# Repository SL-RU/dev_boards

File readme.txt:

This board is for almost any STM32Fxxx MCU with lqfp64 package. Exactly for: STM32F103RCT6

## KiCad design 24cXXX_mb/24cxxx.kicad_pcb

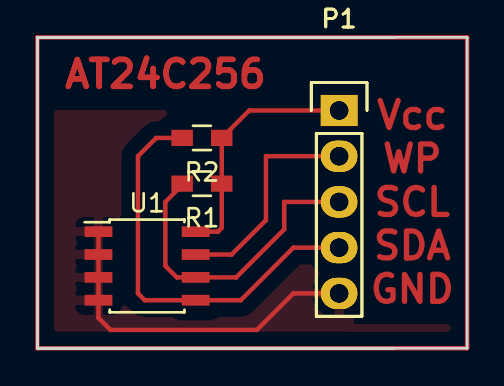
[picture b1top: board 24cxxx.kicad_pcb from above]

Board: 2 copper layers, 23.9 x 17.3 mm, 5 parts (0 on the bottom side), 5 nets.

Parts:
P1, P1#2: CONN_01X05; Pin_Header_Straight_1x05
R1, R2: 4.7k; R_0603_HandSoldering
U1: 24C512; SOIC-8_3.9x4.9mm_Pitch1.27mm

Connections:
unnamed: P1.1, P1#2.1, R1.1, R2.1, U1.8
unnamed: P1.2, P1#2.2, U1.7
unnamed: P1.3, P1#2.3, R1.2, U1.6
unnamed: P1.4, P1#2.4, R2.2, U1.5
unnamed: P1.5, P1#2.5, U1.1, U1.2, U1.3, U1.4

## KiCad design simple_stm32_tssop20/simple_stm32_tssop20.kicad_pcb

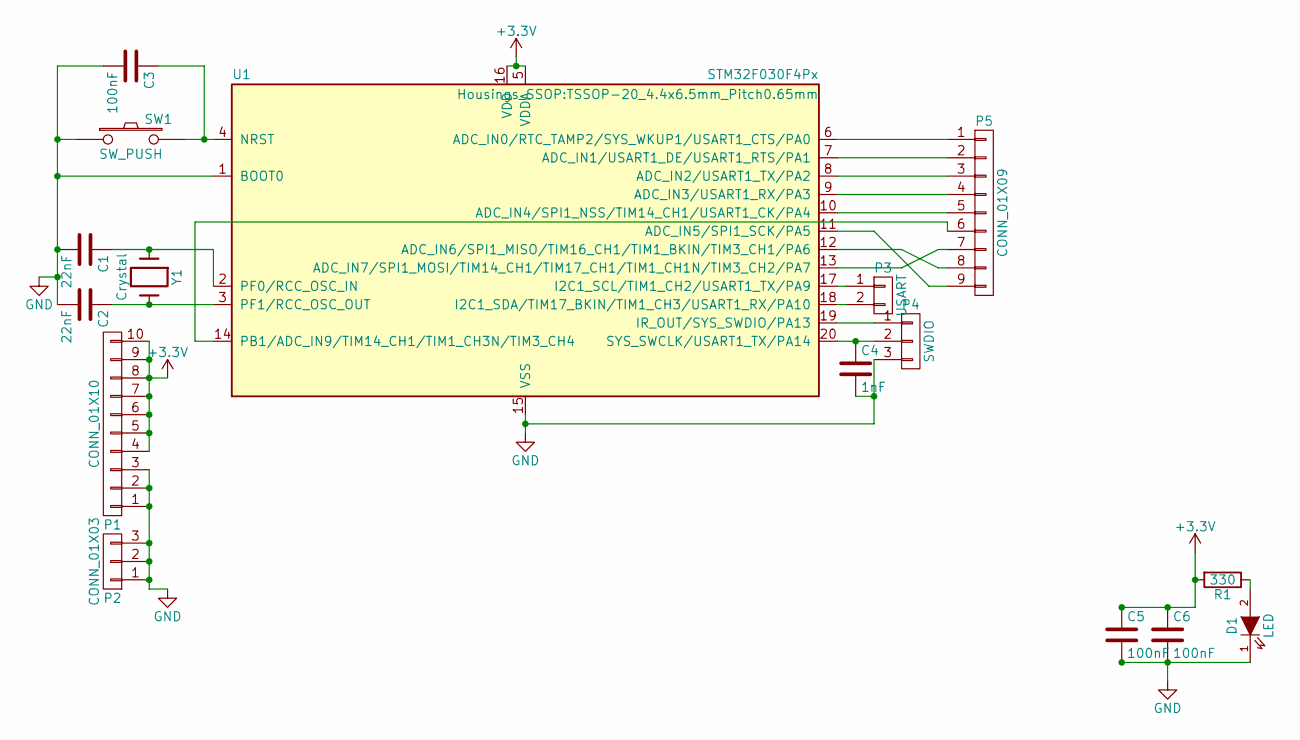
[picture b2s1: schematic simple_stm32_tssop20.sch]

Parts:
C1, C2: 22nF; C_0805_HandSoldering
C3, C5, C6: 100nF; C_0402
C4: 1nF; C_0402
D1: LED; LED-3MM
P1: CONN_01X10; Socket_Strip_Straight_1x10
P2: CONN_01X03; Socket_Strip_Straight_1x03
P3: USART; Socket_Strip_Straight_1x02
P4: SWDIO; Socket_Strip_Straight_1x03
P5: CONN_01X09; Socket_Strip_Straight_1x09
R1: 330; R_0603_HandSoldering
SW1: SW_PUSH; SW_PUSH_SMALL
U1: STM32F030F4Px; TSSOP-20_4.4x6.5mm_Pitch0.65mm
Y1: Crystal; Crystal_HC49-U_Vertical

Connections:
+3V3: C5.1, C6.1, P1.4, P1.5, P1.6, P1.7, P1.8, P1.9, P1.10, R1.2, U1.5 (VDDA), U1.16 (VDD)
GND: C1.2, C2.2, C3.2, C4.2, C5.2, C6.2, D1.1 (K), P1.1, P1.2, P1.3, P2.1, P2.2, P2.3, P4.3, SW1.1, U1.1 (BOOT0), U1.15 (VSS)
unnamed: C1.1, U1.2 (PF0/RCC_OSC_IN), Y1.1
unnamed: C2.1, U1.3 (PF1/RCC_OSC_OUT), Y1.2
unnamed: C3.1, SW1.2, U1.4 (NRST)
unnamed: C4.1, P4.2, U1.20 (SYS_SWCLK/USART1_TX/PA14)
unnamed: D1.2 (A), R1.1
unnamed: P3.1, U1.17 (I2C1_SCL/TIM1_CH2/USART1_TX/PA9)
unnamed: P3.2, U1.18 (I2C1_SDA/TIM17_BKIN/TIM1_CH3/USART1_RX/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)
unnamed: P4.1, U1.19 (IR_OUT/SYS_SWDIO/PA13)
unnamed: P5.1, U1.6 (ADC_IN0/RTC_TAMP2/SYS_WKUP1/USART1_CTS/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)
unnamed: P5.2, U1.7 (ADC_IN1/USART1_DE/USART1_RTS/PA1)
unnamed: P5.3, U1.8 (ADC_IN2/USART1_TX/PA2)
unnamed: P5.4, U1.9 (ADC_IN3/USART1_RX/PA3)
unnamed: P5.5, U1.10 (ADC_IN4/SPI1_NSS/TIM14_CH1/USART1_CK/PA4)
unnamed: P5.6, U1.14 (PB1/ADC_IN9/TIM14_CH1/TIM1_CH3N/TIM3_CH4)
unnamed: P5.7, U1.13 (ADC_IN7/SPI1_MOSI/TIM14_CH1/TIM17_CH1/T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)
unnamed: P5.8, U1.12 (ADC_IN6/SPI1_MISO/TIM16_CH1/TIM1_BKIN/T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)
unnamed: P5.9, U1.11 (ADC_IN5/SPI1_SCK/PA5)

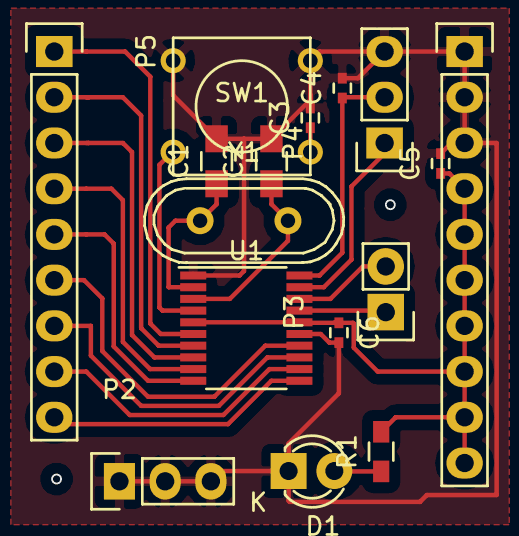
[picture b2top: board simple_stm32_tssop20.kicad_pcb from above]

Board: 2 copper layers, 16 parts (0 on the bottom side), 19 nets.

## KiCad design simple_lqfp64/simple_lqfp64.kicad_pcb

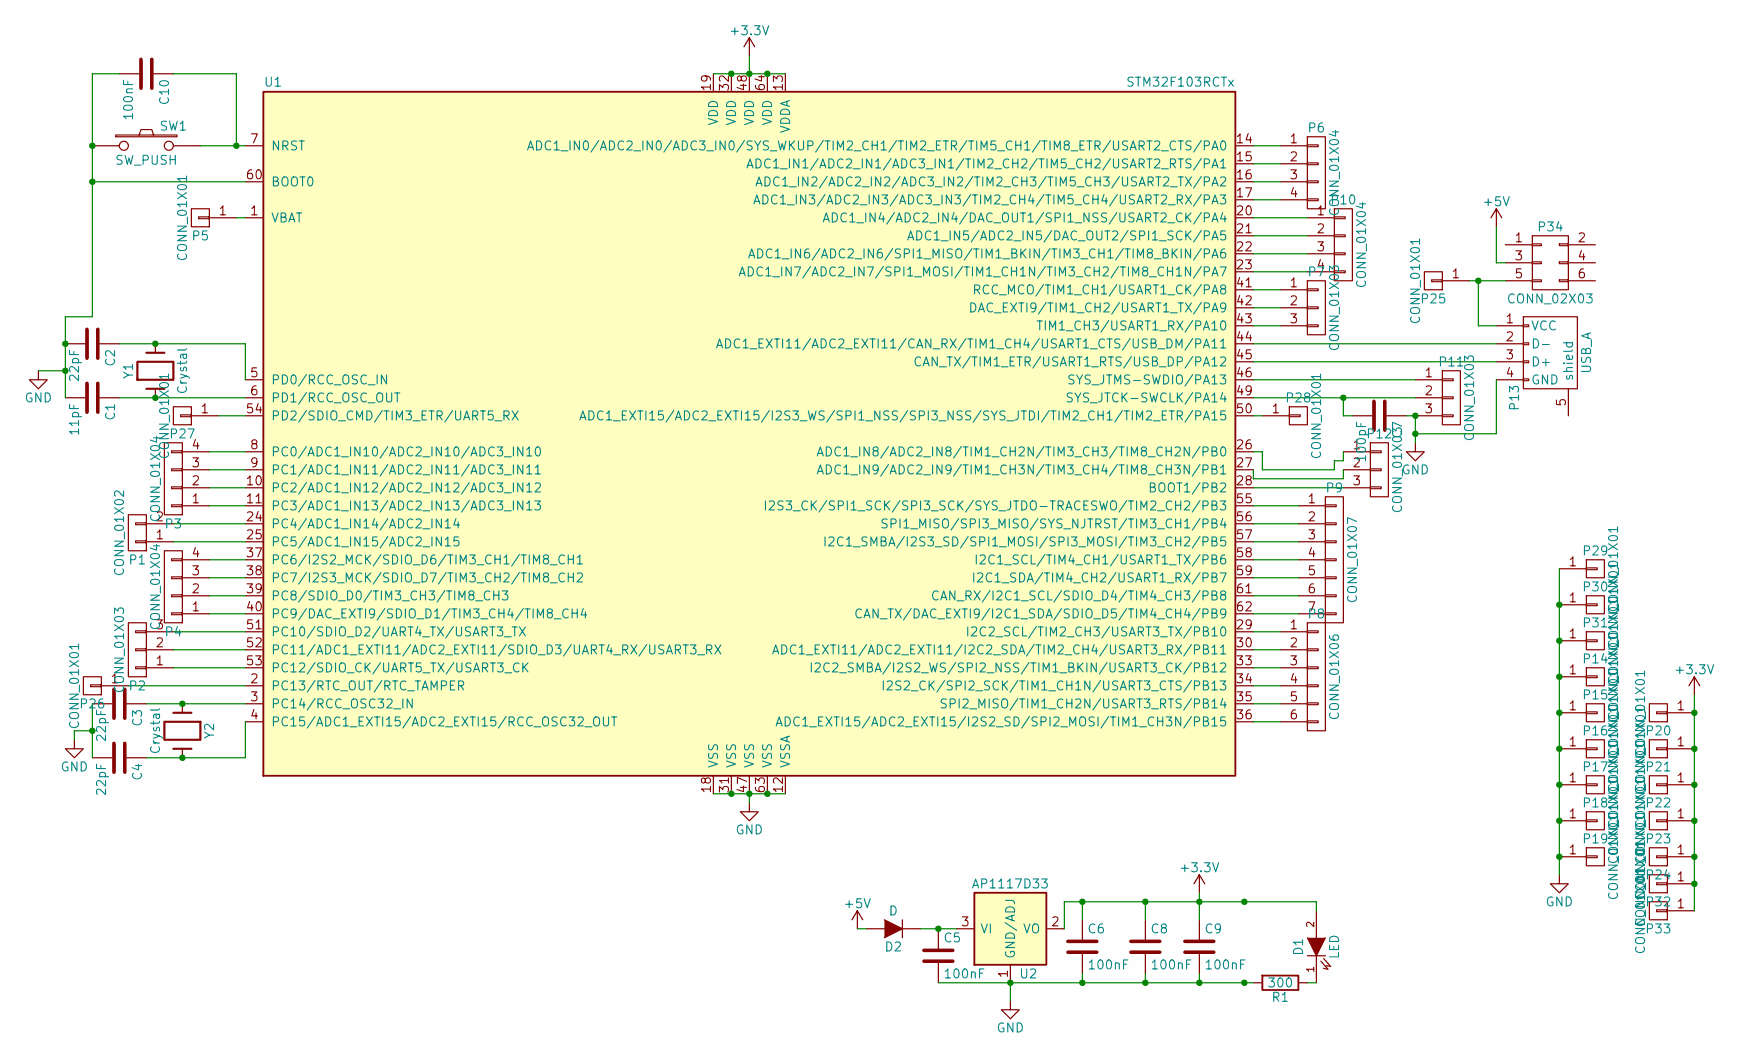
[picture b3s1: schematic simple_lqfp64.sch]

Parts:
C1: 11pF; C_0805_HandSoldering
C2, C3, C4: 22pF; C_0805_HandSoldering
C5, C6, C8, C9, C10: 100nF; C_0805_HandSoldering
C7: 100pF; C_0805_HandSoldering
D1: LED; LED-3MM
D2: D; Diode_DO-35_SOD27_Horizontal_RM10
P1: CONN_01X02; Pin_Header_Straight_1x02
P2, P7, P11, P12: CONN_01X03; Pin_Header_Straight_1x03
P3, P4, P6, P10: CONN_01X04; Pin_Header_Straight_1x04
P5, P14, P15, P16, P17, P18, P19, P20, P21, P22, P23, P24, P25, P26, P27, P28, P29, P30, P31, P32, P33: CONN_01X01; Pin_Header_Straight_1x01
P8: CONN_01X06; Pin_Header_Straight_1x06
P9: CONN_01X07; Pin_Header_Straight_1x07
P13: USB_A; USB_Mini-B
P34: CONN_02X03; Socket_Strip_Straight_2x03
R1: 300; R_0603_HandSoldering
SW1: SW_PUSH; SW_PUSH_SMALL
U1: STM32F103RCTx; LQFP-64_10x10mm_Pitch0.5mm
U2: AP1117D33; SOT89-3_Housing_Handsoldering
Y1: Crystal; Crystal_HC49-U_Vertical
Y2: Crystal; Crystal_Watch

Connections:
+3V3: C6.1, C8.1, C9.1, D1.2 (A), P20.1, P21.1, P22.1, P23.1, P24.1, P32.1, P33.1, U1.13 (VDDA), U1.19 (VDD), U1.32 (VDD), U1.48 (VDD), U1.64 (VDD), U2.2 (VO)
+5V: D2.2 (A), P34.3
GND: C1.2, C2.2, C3.2, C4.2, C5.2, C6.2, C7.1, C8.2, C9.2, C10.2, P11.3, P13.4 (GND), P14.1, P15.1, P16.1, P17.1, P18.1, P19.1, P29.1, P30.1, P31.1, R1.2, SW1.1, U1.12 (VSSA), U1.18 (VSS), U1.31 (VSS), U1.47 (VSS), U1.60 (BOOT0), U1.63 (VSS), U2.1 (GND/ADJ)
unnamed: C1.1, U1.6 (PD1/RCC_OSC_OUT), Y1.1
unnamed: C2.1, U1.5 (PD0/RCC_OSC_IN), Y1.2
unnamed: C3.1, U1.3 (PC14/RCC_OSC32_IN), Y2.1
unnamed: C4.1, U1.4 (PC15/ADC1_EXTI15/ADC2_EXTI15/RCC_OSC32_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), Y2.2
unnamed: C5.1, D2.1 (K), U2.3 (VI)
unnamed: C7.2, P11.2, U1.49 (SYS_JTCK-SWCLK/PA14)
unnamed: C10.1, SW1.2, U1.7 (NRST)
unnamed: D1.1 (K), R1.1
unnamed: P1.1, U1.25 (PC5/ADC1_IN15/ADC2_IN15)
unnamed: P1.2, U1.24 (PC4/ADC1_IN14/ADC2_IN14)
unnamed: P2.1, U1.53 (PC12/SDIO_CK/UART5_TX/USART3_CK)
unnamed: P2.2, U1.52 (PC11/ADC1_EXTI11/ADC2_EXTI11/SDIO_D3/UA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)
unnamed: P2.3, U1.51 (PC10/SDIO_D2/UART4_TX/USART3_TX)
unnamed: P3.1, U1.11 (PC3/ADC1_IN13/ADC2_IN13/ADC3_IN13)
unnamed: P3.2, U1.10 (PC2/ADC1_IN12/ADC2_IN12/ADC3_IN12)
unnamed: P3.3, U1.9 (PC1/ADC1_IN11/ADC2_IN11/ADC3_IN11)
unnamed: P3.4, U1.8 (PC0/ADC1_IN10/ADC2_IN10/ADC3_IN10)
unnamed: P4.1, U1.40 (PC9/DAC_EXTI9/SDIO_D1/TIM3_CH4/TIM8_CH4)
unnamed: P4.2, U1.39 (PC8/SDIO_D0/TIM3_CH3/TIM8_CH3)
unnamed: P4.3, U1.38 (PC7/I2S3_MCK/SDIO_D7/TIM3_CH2/TIM8_CH2)
unnamed: P4.4, U1.37 (PC6/I2S2_MCK/SDIO_D6/TIM3_CH1/TIM8_CH1)
unnamed: P5.1, U1.1 (VBAT)
unnamed: P6.1, U1.14 (ADC1_IN0/ADC2_IN0/ADC3_IN0/SYS_WKUP/TIM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)
unnamed: P6.2, U1.15 (ADC1_IN1/ADC2_IN1/ADC3_IN1/TIM2_CH2/TIM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)
unnamed: P6.3, U1.16 (ADC1_IN2/ADC2_IN2/ADC3_IN2/TIM2_CH3/TIM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)
unnamed: P6.4, U1.17 (ADC1_IN3/ADC2_IN3/ADC3_IN3/TIM2_CH4/TIM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)
unnamed: P7.1, U1.41 (RCC_MCO/TIM1_CH1/USART1_CK/PA8)
unnamed: P7.2, U1.42 (DAC_EXTI9/TIM1_CH2/USART1_TX/PA9)
unnamed: P7.3, U1.43 (TIM1_CH3/USART1_RX/PA10)
unnamed: P8.1, U1.29 (I2C2_SCL/TIM2_CH3/USART3_TX/PB10)
unnamed: P8.2, U1.30 (ADC1_EXTI11/ADC2_EXTI11/I2C2_SDA/TIM2_C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)
unnamed: P8.3, U1.33 (I2C2_SMBA/I2S2_WS/SPI2_NSS/TIM1_BKIN/US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)
unnamed: P8.4, U1.34 (I2S2_CK/SPI2_SCK/TIM1_CH1N/USART3_CTS/P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)
unnamed: P8.5, U1.35 (SPI2_MISO/TIM1_CH2N/USART3_RTS/PB14)
unnamed: P8.6, U1.36 (ADC1_EXTI15/ADC2_EXTI15/I2S2_SD/SPI2_MO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)
unnamed: P9.1, U1.55 (I2S3_CK/SPI1_SCK/SPI3_SCK/SYS_JTDO-TRAC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)
unnamed: P9.2, U1.56 (SPI1_MISO/SPI3_MISO/SYS_NJTRST/TIM3_CH1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)
unnamed: P9.3, U1.57 (I2C1_SMBA/I2S3_SD/SPI1_MOSI/SPI3_MOSI/T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)
unnamed: P9.4, U1.58 (I2C1_SCL/TIM4_CH1/USART1_TX/PB6)
unnamed: P9.5, U1.59 (I2C1_SDA/TIM4_CH2/USART1_RX/PB7)
unnamed: P9.6, U1.61 (CAN_RX/I2C1_SCL/SDIO_D4/TIM4_CH3/PB8)
unnamed: P9.7, U1.62 (CAN_TX/DAC_EXTI9/I2C1_SDA/SDIO_D5/TIM4_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)
unnamed: P10.1, U1.20 (ADC1_IN4/ADC2_IN4/DAC_OUT1/SPI1_NSS/USA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)
unnamed: P10.2, U1.21 (ADC1_IN5/ADC2_IN5/DAC_OUT2/SPI1_SCK/PA5)
unnamed: P10.3, U1.22 (ADC1_IN6/ADC2_IN6/SPI1_MISO/TIM1_BKIN/T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)
unnamed: P10.4, U1.23 (ADC1_IN7/ADC2_IN7/SPI1_MOSI/TIM1_CH1N/T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)
unnamed: P11.1, U1.46 (SYS_JTMS-SWDIO/PA13)
unnamed: P12.1, U1.26 (ADC1_IN8/ADC2_IN8/TIM1_CH2N/TIM3_CH3/TI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)
unnamed: P12.2, U1.27 (ADC1_IN9/ADC2_IN9/TIM1_CH3N/TIM3_CH4/TI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)
unnamed: P12.3, U1.28 (BOOT1/PB2)
unnamed: P13.1 (VCC), P25.1, P34.5
unnamed: P13.2 (D-), U1.44 (ADC1_EXTI11/ADC2_EXTI11/CAN_RX/TIM1_CH4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)
unnamed: P13.3 (D+), U1.45 (CAN_TX/TIM1_ETR/USART1_RTS/USB_DP/PA12)
unnamed: P26.1, U1.2 (PC13/RTC_OUT/RTC_TAMPER)
unnamed: P27.1, U1.54 (PD2/SDIO_CMD/TIM3_ETR/UART5_RX)
unnamed: P28.1, U1.50 (ADC1_EXTI15/ADC2_EXTI15/I2S3_WS/SPI1_NS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)

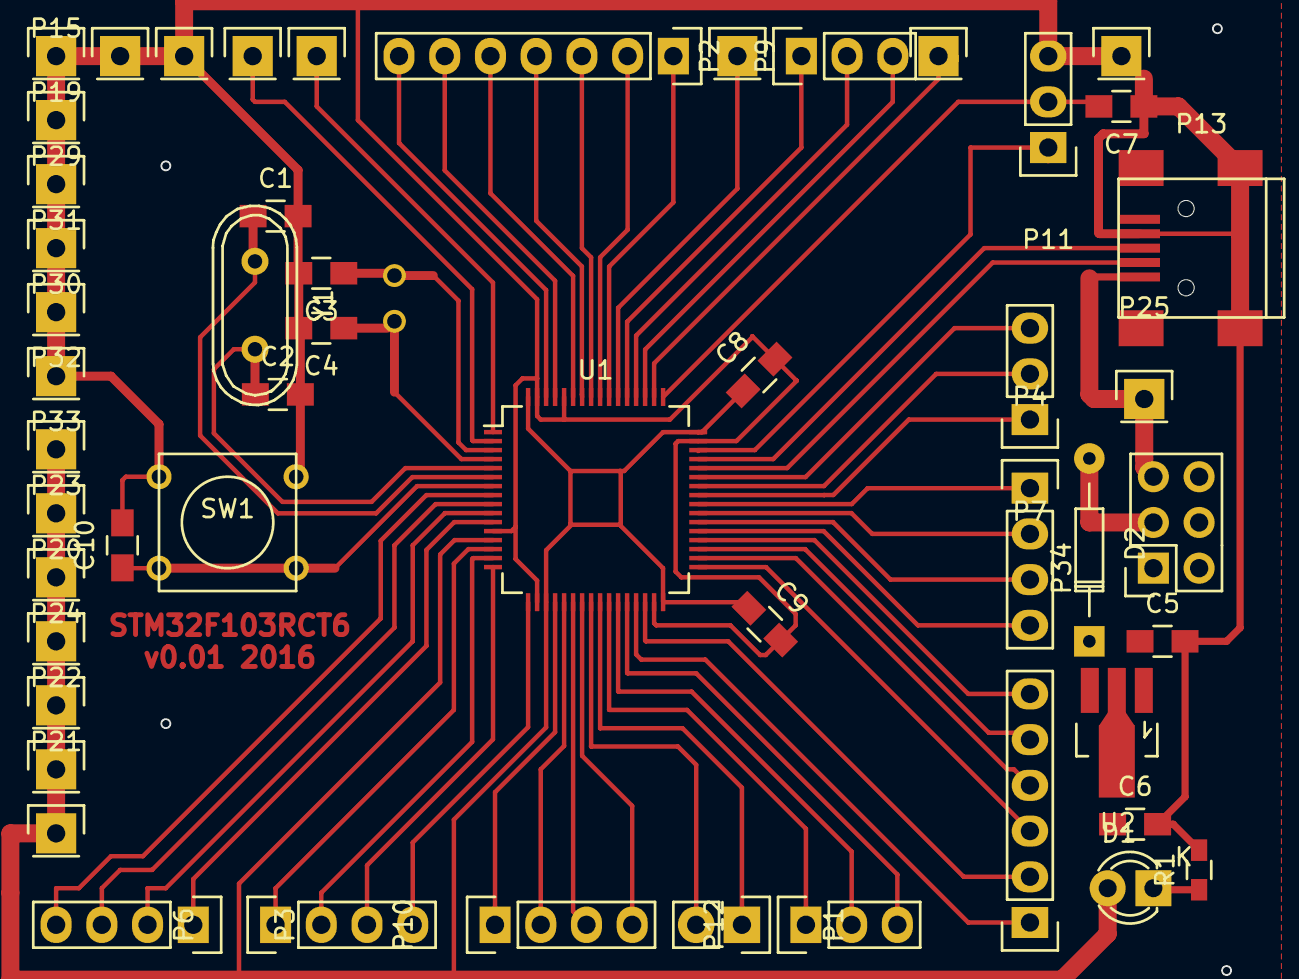
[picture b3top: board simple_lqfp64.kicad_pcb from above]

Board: 2 copper layers, 52 parts (1 on the bottom side), 59 nets.

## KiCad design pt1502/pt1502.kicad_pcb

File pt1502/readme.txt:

THIS IC IS AWFUL!
DO NOT EVER USE IT IN YOUR PROJECTS11!

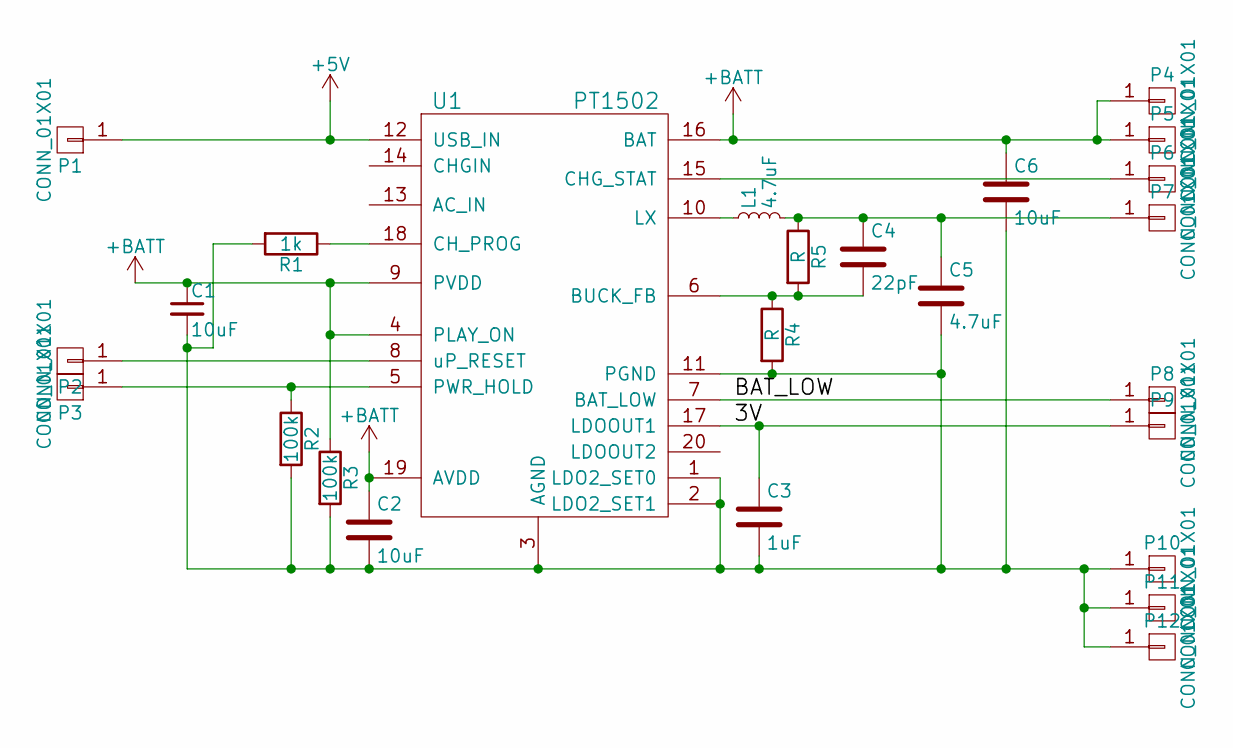
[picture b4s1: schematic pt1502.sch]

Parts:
C1, C2, C6: 10uF; C_Radial_D6.3_L11.2_P2.5
C3: 1uF; C_Radial_D6.3_L11.2_P2.5
C4: 22pF; C_0805_HandSoldering
C5: 4.7uF; C_Radial_D6.3_L11.2_P2.5
L1: 4.7uF; C_Radial_D6.3_L11.2_P2.5
P1, P2, P3, P4, P5, P6, P7, P8, P9, P10, P11, P12: CONN_01X01; Socket_Strip_Straight_1x01
R1: 1k; Resistor_Horizontal_RM10mm
R2, R3: 100k; R_0603_HandSoldering
R4, R5: R; R_0603_HandSoldering
U1: PT1502; QFN-20-1EP_4x4mm_Pitch0.5mm

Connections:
+5V: P1.1, U1.12 (USB_IN)
+BATT: C1.1, C2.1, C6.1, P4.1, P5.1, R3.1, U1.4 (PLAY_ON), U1.9 (PVDD), U1.16 (BAT), U1.19 (AVDD)
/3V: C3.1, P9.1, U1.17 (LDOOUT1)
/BAT_LOW: P8.1, U1.7 (BAT_LOW)
unnamed: C1.2, C2.2, C3.2, C5.2, C6.2, P10.1, P11.1, P12.1, R1.2, R2.2, R3.2, R4.2, U1.1 (LDO2_SET0), U1.2 (LDO2_SET1), U1.3 (AGND), U1.11 (PGND)
unnamed: C4.1, C5.1, L1.2, P7.1, R5.1
unnamed: C4.2, R4.1, R5.2, U1.6 (BUCK_FB)
unnamed: L1.1, U1.10 (LX)
unnamed: P2.1, U1.8 (uP_RESET)
unnamed: P3.1, R2.1, U1.5 (PWR_HOLD)
unnamed: P6.1, U1.15 (CHG_STAT)
unnamed: R1.1, U1.18 (CH_PROG)

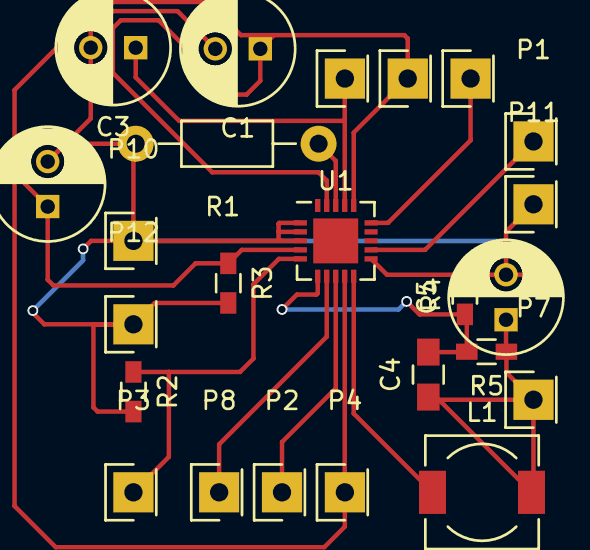
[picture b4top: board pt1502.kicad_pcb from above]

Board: 2 copper layers, 24 parts (0 on the bottom side), 12 nets.

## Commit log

2016-03-23 stm32f103rct6 simple circuit
2016-03-30 stm32 lqfp64 fixes
2016-03-30 save
2016-04-04 lqfp64 release
2016-04-22 charger libs
2016-05-09 bq29330
